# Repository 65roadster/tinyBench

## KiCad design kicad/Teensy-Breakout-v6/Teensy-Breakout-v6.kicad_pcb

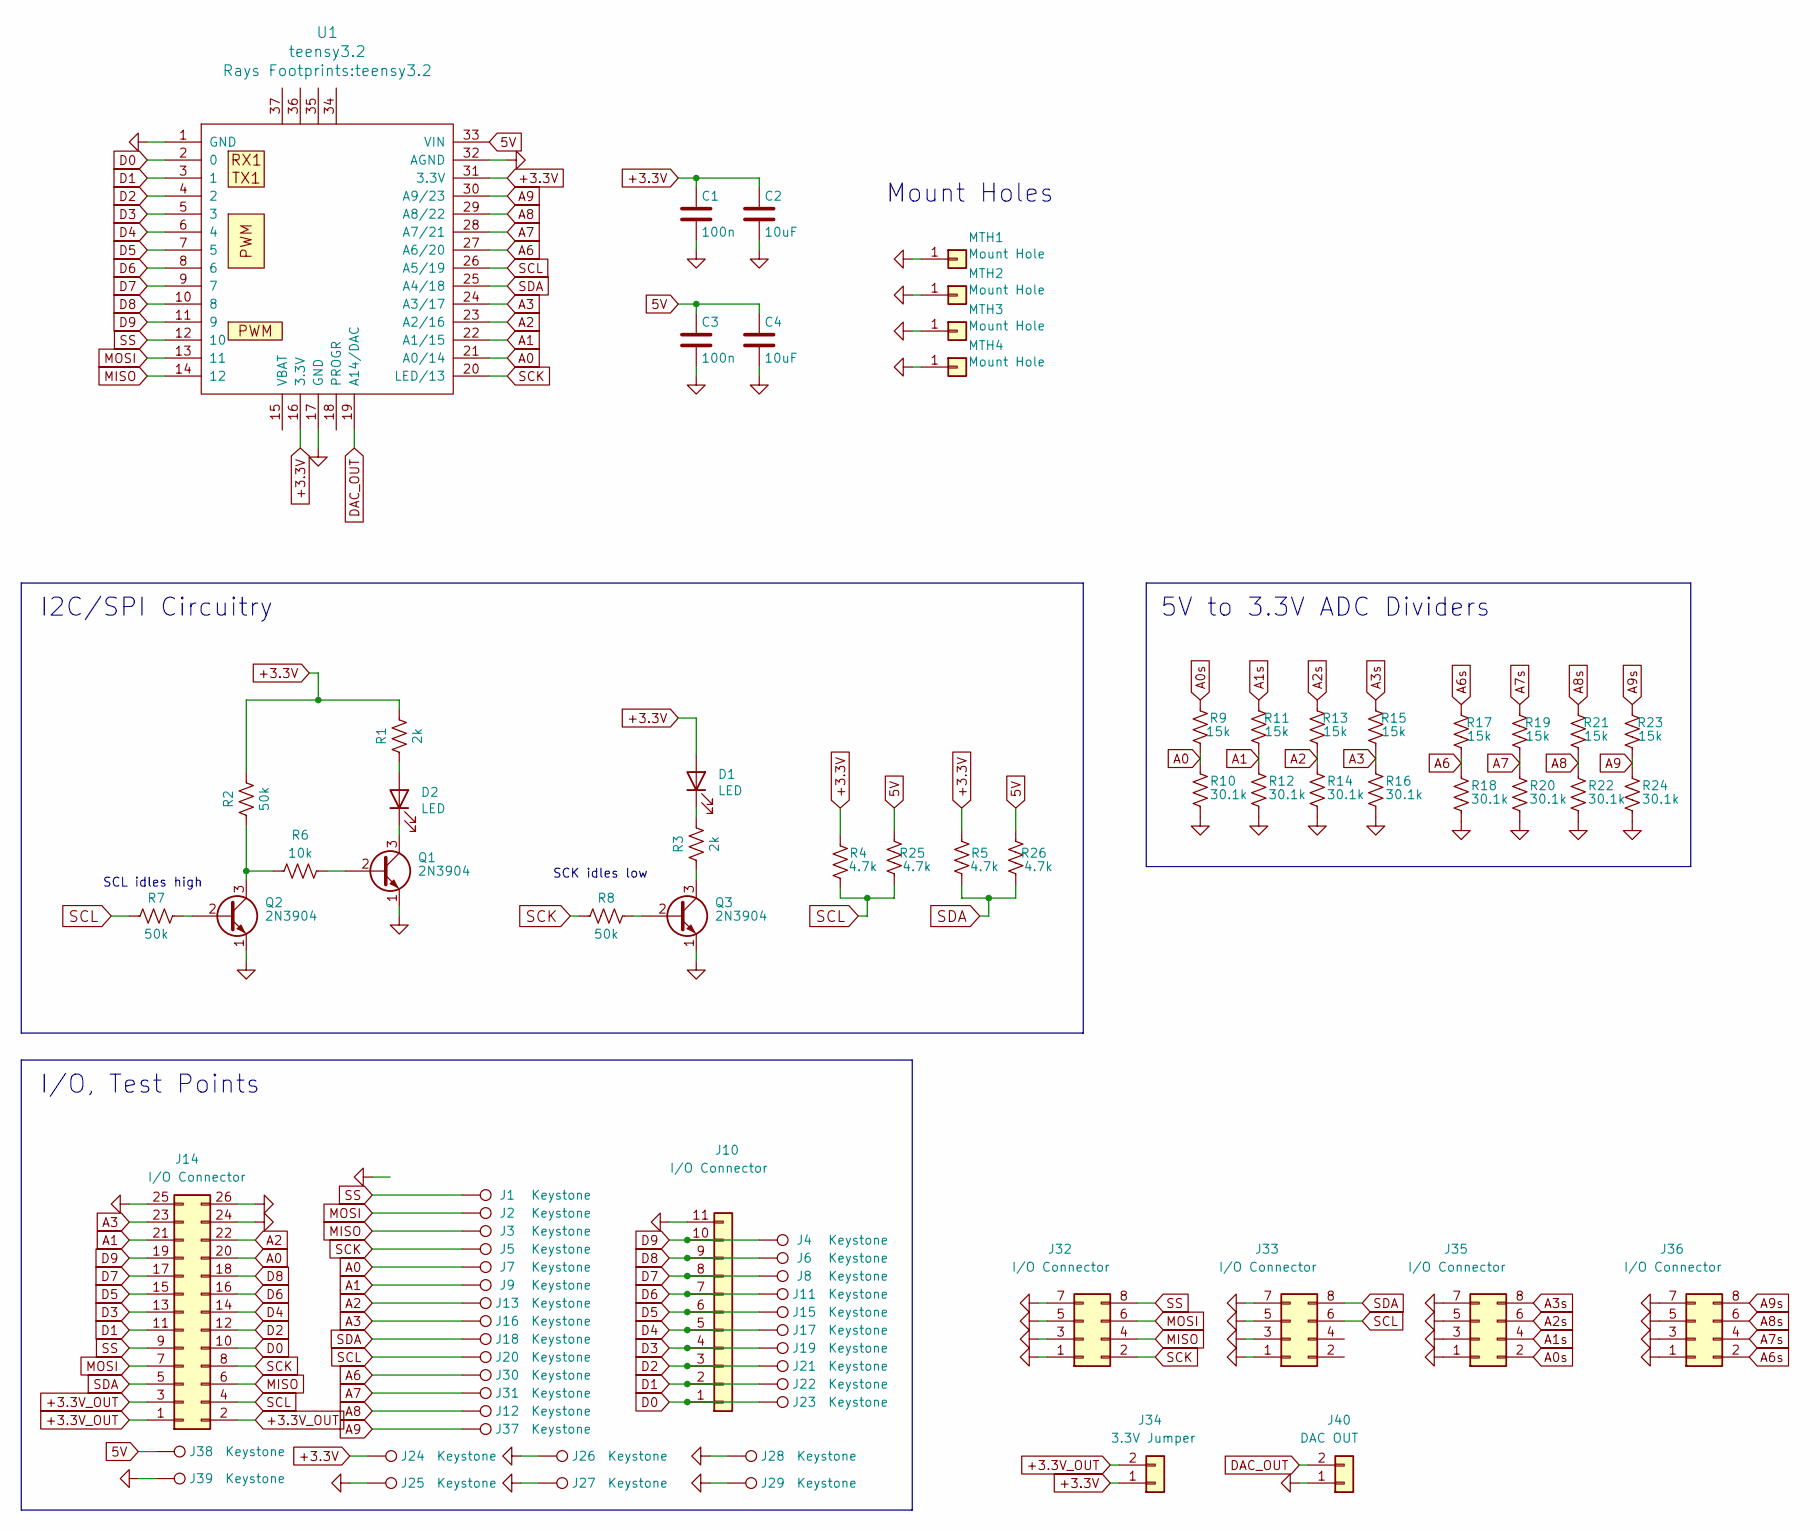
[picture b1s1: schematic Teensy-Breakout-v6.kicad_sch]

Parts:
C1, C3: 100n; C_0805_HandSoldering
C2, C4: 10uF; C_0805_HandSoldering
D1, D2: LED; LED_0805_2012Metric_Pad1.15x1.40mm_HandSolder
J1, J2, J3, J4, J5, J6, J7, J8, J9, J11, J12, J13, J15, J16, J17, J18, J19, J20, J21, J22, J23, J24, J25, J26, J27, J28, J29, J30, J31, J37, J38, J39: Keystone; Keystone-5005
J10: I/O Connector; PinHeader_1x11_P2.54mm_Vertical
J14: I/O Connector; Conn_Samtech_EHF-113-01-L-D
J32, J33, J35, J36: I/O Connector; PinHeader_2x04_P2.54mm_Vertical
J34: 3.3V Jumper; PinHeader_1x02_P2.54mm_Vertical
J40: DAC OUT; PinHeader_1x02_P2.54mm_Vertical
MTH1, MTH2, MTH3, MTH4: Mount Hole; Mount-Hole-#6
Q1, Q2, Q3: 2N3904; 2N3904-SOT-23
R1, R3: 2k; R_0805_HandSoldering
R2, R7, R8: 50k; R_0805_HandSoldering
R4, R5, R25, R26: 4.7k; R_0805_HandSoldering
R6: 10k; R_0805_HandSoldering
R9, R11, R13, R15, R17, R19, R21, R23: 15k; R_0603_HandSoldering
R10, R12, R14, R16, R18, R20, R22, R24: 30.1k; R_0603_HandSoldering
U1: teensy3.2

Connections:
5V: C3.1, C4.1, J38.1, R25.2, R26.2, U1.33 (VIN)
+3.3V: C1.1, C2.1, D1.2 (A), J24.1, J34.1, R1.2, R2.1, R4.2, R5.2, U1.16 (3.3V), U1.31 (3.3V)
+3.3V_OUT: J14.1, J14.2, J14.3, J34.2
A0: J7.1, J14.20, R9.1, R10.2, U1.21 (A0/14)
A0s: J35.2, R9.2
A1: J9.1, J14.21, R11.1, R12.2, U1.22 (A1/15)
A1s: J35.4, R11.2
A2: J13.1, J14.22, R13.1, R14.2, U1.23 (A2/16)
A2s: J35.6, R13.2
A3: J14.23, J16.1, R15.1, R16.2, U1.24 (A3/17)
A3s: J35.8, R15.2
A6: J30.1, R17.1, R18.2, U1.27 (A6/20)
A6s: J36.2, R17.2
A7: J31.1, R19.1, R20.2, U1.28 (A7/21)
A7s: J36.4, R19.2
A8: J12.1, R21.1, R22.2, U1.29 (A8/22)
A8s: J36.6, R21.2
A9: J37.1, R23.1, R24.2, U1.30 (A9/23)
A9s: J36.8, R23.2
D0: J10.1, J14.10, J23.1, U1.2 (0)
D1: J10.2, J14.11, J22.1, U1.3 (1)
D2: J10.3, J14.12, J21.1, U1.4 (2)
D3: J10.4, J14.13, J19.1, U1.5 (3)
D4: J10.5, J14.14, J17.1, U1.6 (4)
D5: J10.6, J14.15, J15.1, U1.7 (5)
D6: J10.7, J11.1, J14.16, U1.8 (6)
D7: J8.1, J10.8, J14.17, U1.9 (7)
D8: J6.1, J10.9, J14.18, U1.10 (8)
D9: J4.1, J10.10, J14.19, U1.11 (9)
DAC_OUT: J40.2, U1.19 (A14/DAC)
GND: C1.2, C2.2, C3.2, C4.2, J10.11, J14.24, J14.25, J14.26, J25.1, J26.1, J27.1, J28.1, J29.1, J32.1, J32.3, J32.5, J32.7, J33.1, J33.3, J33.5, J33.7, J35.1, J35.3, J35.5, J35.7, J36.1, J36.3, J36.5, J36.7, J39.1, J40.1, MTH1.1, MTH2.1, MTH3.1, MTH4.1, Q1.1 (E), Q2.1 (E), Q3.1 (E), R10.1, R12.1, R14.1, R16.1, R18.1, R20.1, R22.1, R24.1, U1.1 (GND), U1.17 (GND), U1.32 (AGND)
MISO: J3.1, J14.6, J32.4, U1.14 (12)
MOSI: J2.1, J14.7, J32.6, U1.13 (11)
unnamed: D1.1 (K), R3.2
unnamed: D2.1 (K), Q1.3 (C)
unnamed: D2.2 (A), R1.1
unnamed: Q1.2 (B), R6.2
unnamed: Q2.2 (B), R7.2
unnamed: Q2.3 (C), R2.2, R6.1
unnamed: Q3.2 (B), R8.2
unnamed: Q3.3 (C), R3.1
SCK: J5.1, J14.8, J32.2, R8.1, U1.20 (LED/13)
SCL: J14.4, J20.1, J33.6, R4.1, R7.1, R25.1, U1.26 (A5/19)
SDA: J14.5, J18.1, J33.8, R5.1, R26.1, U1.25 (A4/18)
SS: J1.1, J14.9, J32.8, U1.12 (10)

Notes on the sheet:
5V to 3.3V ADC Dividers
Mount Holes
I/O, Test Points
SCK idles low
I2C/SPI Circuitry
SCL idles high

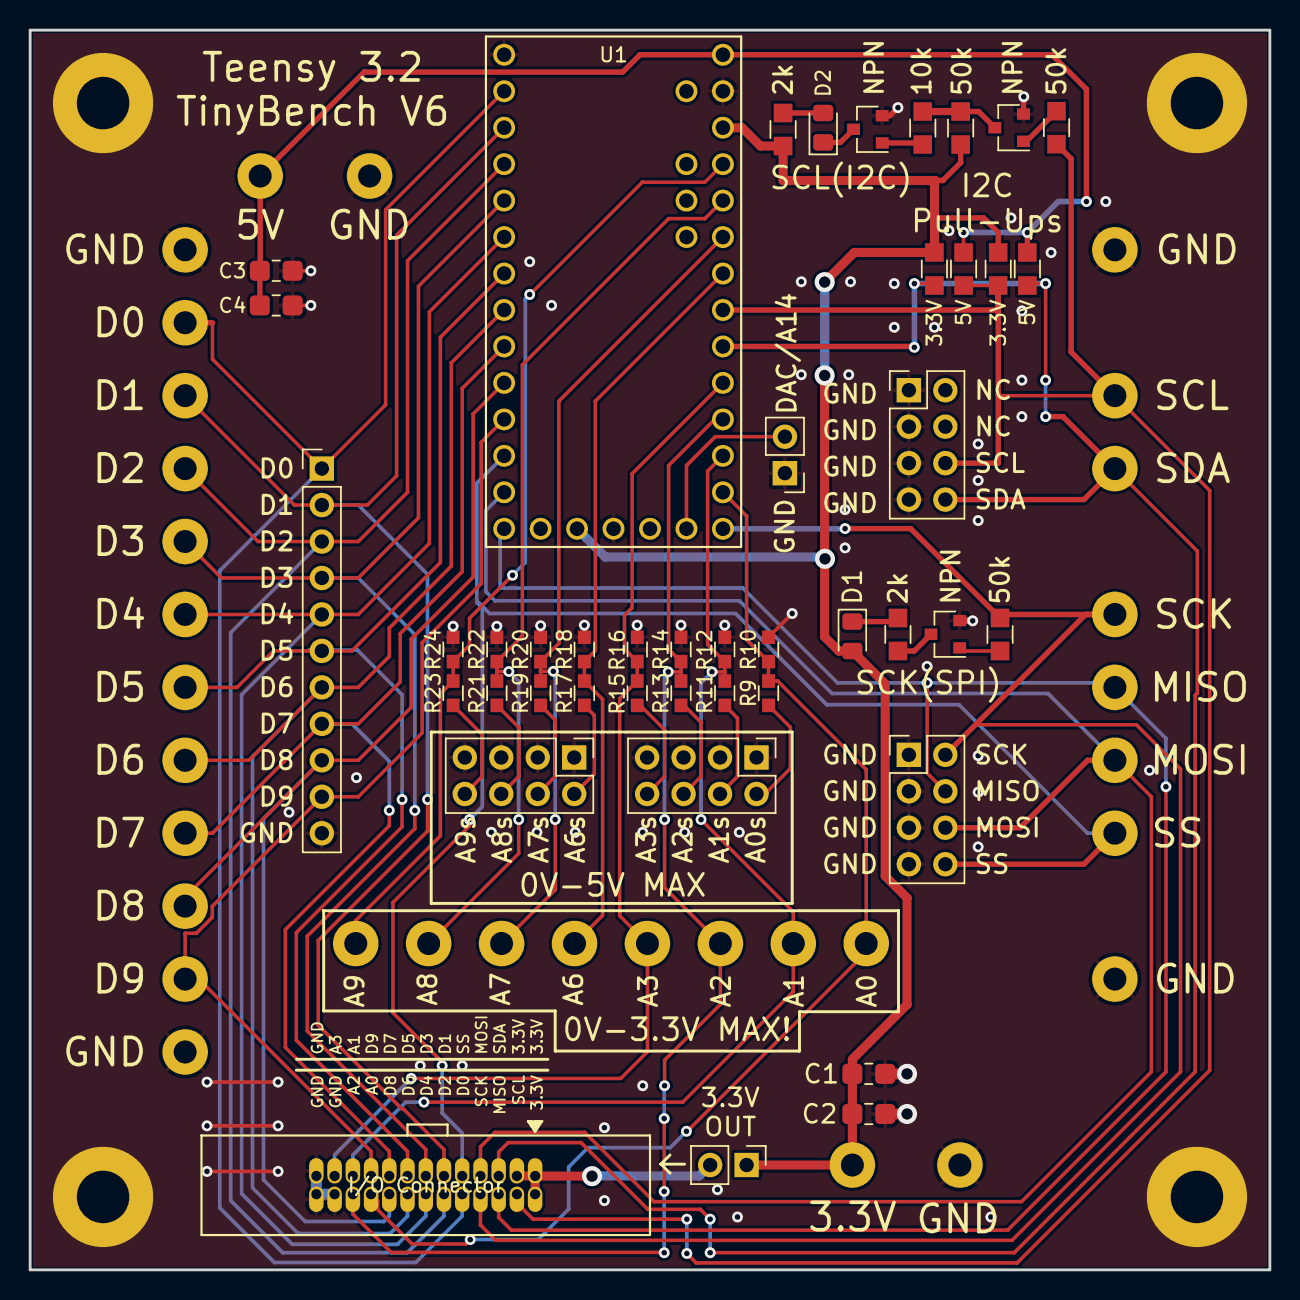
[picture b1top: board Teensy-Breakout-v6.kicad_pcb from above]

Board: 2 copper layers, 86.4 x 86.4 mm, 80 parts (0 on the bottom side), 45 nets.

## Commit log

2022-10-16 initial publish
2022-10-19 Update with KiCAD Files
2023-03-09 Added V6

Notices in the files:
parts and their libraries:
Copyright 2016 Accelerated Designs. All rights reserved.
